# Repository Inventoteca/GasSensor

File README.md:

# Gas Sensor
Sensor de nivel de gas para tanques estacionarios. Se coloca sobre 
el indicador de nivel y transmite las lectura de manera inalámbrica. 
Hay 2 versiones principales: uno que usa LoRa y otro que usa Sigfox.  

La versión LoRa no es viable porque necesita muchas estaciones disponibles.  
La versión Sigfox funciona.  

Debe funcionar durante 3 años continuos usando 2 baterías AA. 
Se necesita un consumo promedio de 4 mA o menos.

El diseño "sensor_sigfox_1.1" es una actualización de la versión 1 del sensor Sigfox. 
Se han realizado cmabios en hardware y software . Los cambios principales son:  
- los módulos están configurados en modo de bajo consumo
- la lectura del voltaje de alimentación se realiza con el hardware interno del microcontrolador (de esta forma se elimina un divisor de voltaje externo)
- cambio de sensor magnético (se descarta el AS5600 y se agrega el MLX90393)
- usar frecuencia de reloj de ultra-bajo consumo (32.768 kHz)
- se puede usar el generador de frecuencia interno, pero también se agrega un cristal y capacitores de carga para commparar el consumo
- eliminar booster
- agregar conector U.FL para antena y pad para soldar antena de alambre opcional (eliminar conector SMA)

El conector U.FL se usa en muchos dispositivos  
https://en.wikipedia.org/wiki/Hirose_U.FL  
https://learn.sparkfun.com/tutorials/three-quick-tips-about-using-ufl/all  
https://www.data-alliance.net/ufl-cables/  

Los cristales más baratos tienen encapsulado cilindrico  
https://www.lcsc.com/product-detail/Crystals_CREC-01-X-TB-11CHJRI032768000_C7462599.html  
Para facilitar el montaje se usarán cristales SMD aunque son un poco más grandes  
https://www.lcsc.com/product-detail/Crystals_huaxindianzi-DP2032K76812001_C17702403.html  

El microcontrolador es ATtiny826 (8kB, family 2, 20 pins). Se usan los siguiente pines:  
- alimentación VCC pin 1, GND pin 20
- I2C (TWI) SDA pin 10 PB1, SCL pin 11 PB0
- cristal TOSC1 pin 8 PB3, TOSC2 pin 9 PB2
- UART hay 2 puertos con pines configurables (Serial y Serial1) con TX, RX, XCK, XDIR en PC0, PC1, PC2, PC3 y PA1, PA2, PA3, PA4
https://datasheet.lcsc.com/lcsc/2309071123_Microchip-Tech-ATTINY826-XU_C3235639.pdf
https://github.com/SpenceKonde/megaTinyCore

Los componentes más baratos están en LCSC, luego DigiKey y en tercer lugar Mouser  

El sensor Hall se puede usar en modo I2C o SPI. Se usará el modo I2C

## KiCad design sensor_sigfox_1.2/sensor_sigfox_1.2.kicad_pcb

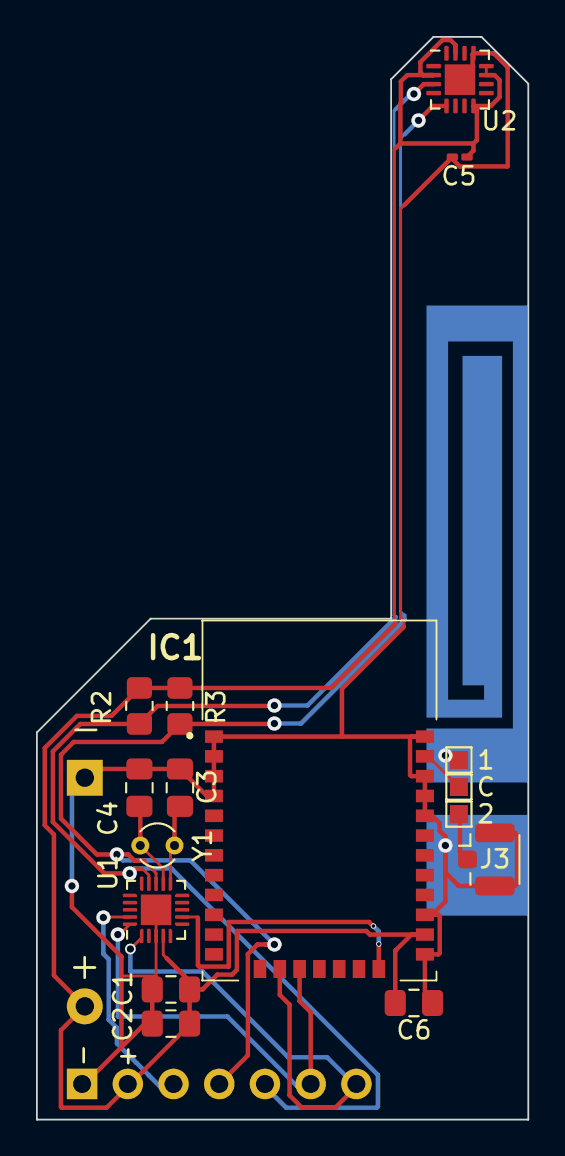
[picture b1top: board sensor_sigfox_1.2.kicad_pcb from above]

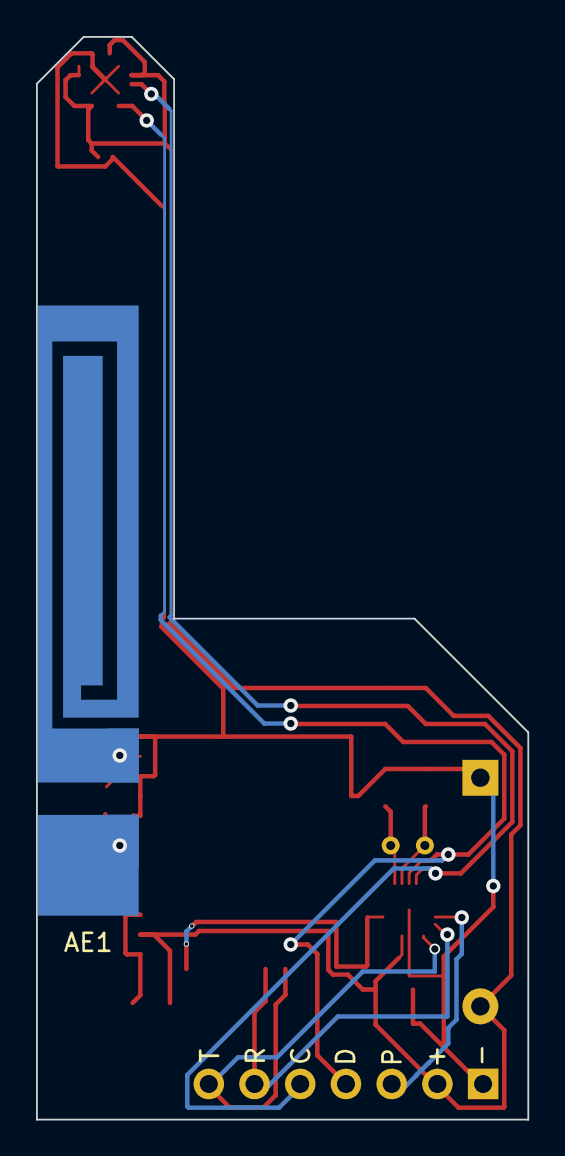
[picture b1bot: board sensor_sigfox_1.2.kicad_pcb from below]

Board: 2 copper layers, 27.3 x 60.1 mm, 19 parts (2 on the bottom side), 13 nets.

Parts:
1, 2: TestPoint; TestPoint_Pad_1.0x1.0mm
AE1: Antenna_Shield; antena1
C: TestPoint; TestPoint_Pad_1.0x1.0mm
C1: 10u; C_0805_2012Metric_Pad1.18x1.45mm_HandSolder
C2, C6: 100n; C_0805_2012Metric_Pad1.18x1.45mm_HandSolder
C3, C4: 20p; C_0805_2012Metric_Pad1.18x1.45mm_HandSolder
C5: 100n; C_0201_0603Metric_Pad0.64x0.40mm_HandSolder
IC1: WSSFM11R2DAT
J1: Battery; BatteryHolder_Keystone_2468_2xAAA
J2: Conn_01x07_Socket; PinHeader_1x07_P2.54mm_Vertical
J3: Conn_Coaxial; U.FL_Hirose_U.FL-R-SMT-1_Vertical
R2, R3: 2.2k; R_0805_2012Metric_Pad1.20x1.40mm_HandSolder
U1: ATtiny826-X; VQFN-20-1EP_3x3mm_P0.4mm_EP1.7x1.7mm
U2: MLX90393; QFN-16-1EP_3x3mm_P0.5mm_EP1.7x1.7mm
Y1: 32.768 kHz; Crystal_C26-LF_D2.1mm_L6.5mm_Vertical

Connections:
/SCL: J2.5, R2.1, U1.14 (PB0), U2.3 (SCL/SCLK)
/SDA: J2.4, R3.1, U1.13 (PB1), U2.5 (SDA/MOSI)
/SF_RX: IC1.15 (UARTRX), J2.6, U1.20 (PA1)
/SF_TX: IC1.14 (UARTTX), J2.7, U1.1 (PA2)
GND: AE1.2 (Shield), C1.1, C2.1, C3.1, C4.1, C5.1, C6.1, IC1.1 (GND_1), IC1.2 (GND_2), IC1.3 (GND_3), IC1.4 (GND_4), IC1.20 (GND_5), IC1.22 (GND_6), IC1.27 (GND_7), IC1.28 (GND_8), IC1.29 (GND_9), IC1.31 (GND_10), J1.1, J2.1, J3.2 (Ext), U1.3 (GND), U1.21 (GND), U2.13 (VSS), U2.17 (PAD)
unnamed: 1.1, AE1.1 (A)
unnamed: C.1, IC1.30 (RF_IO)
unnamed: IC1.19 (RST_N), U1.7 (PA6)
unnamed: J2.3, U1.19 (~RESET/PA0)
unnamed: 2.1, J3.1 (In)
unnamed: C4.2, U1.12 (PB2), Y1.2
unnamed: C3.2, U1.11 (PB3), Y1.1
VCC: C1.2, C2.2, C5.2, C6.2, IC1.21 (VDD_IO), J1.2, J2.2, R2.2, R3.2, U1.4 (VCC), U2.2 (MS/CS), U2.8 (VDD_IO), U2.11 (A1), U2.12 (A0), U2.15 (VDD)

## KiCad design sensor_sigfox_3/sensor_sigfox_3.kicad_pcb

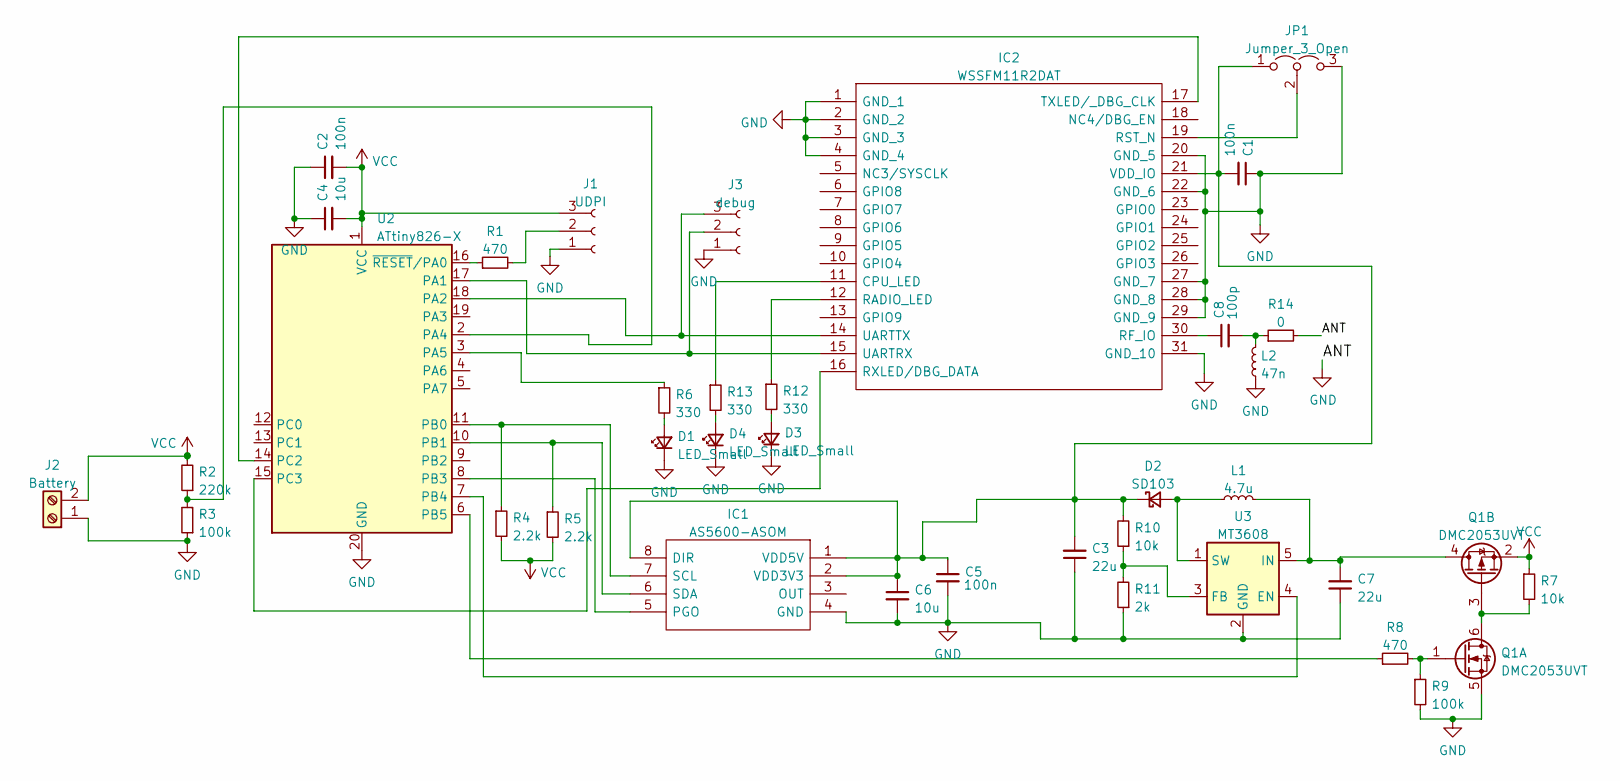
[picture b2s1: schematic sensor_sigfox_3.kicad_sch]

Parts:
C1, C2, C5: 100n; C_0603_1608Metric_Pad1.08x0.95mm_HandSolder
C3, C7: 22u; C_0805_2012Metric_Pad1.18x1.45mm_HandSolder
C4, C6: 10u; C_0603_1608Metric_Pad1.08x0.95mm_HandSolder
C8: 100p; C_0603_1608Metric_Pad1.08x0.95mm_HandSolder
D1, D3, D4: LED_Small; LED_0603_1608Metric_Pad1.05x0.95mm_HandSolder
D2: SD103; D_SMA
IC1: AS5600-ASOM; SOIC127P600X175-8N; Manufacturer_Part_Number AS5600-ASOM; Mouser Part Number 985-AS5600-ASOM
IC2: WSSFM11R2DAT; Manufacturer_Part_Number WSSFM11R2DAT
J1: UDPI; PinHeader_1x03_P2.54mm_Vertical
J2: Battery; PinHeader_1x02_P2.54mm_Horizontal
J3: debug; PinHeader_1x03_P2.54mm_Vertical
JP1: Jumper_3_Open; SolderJumper-3_P1.3mm_Open_Pad1.0x1.5mm
L1: 4.7u; L_Murata_LQH55DN_5.7x5.0mm
L2: 47n; L_0603_1608Metric_Pad1.05x0.95mm_HandSolder
Q1: DMC2053UVT; TSOT-23-6
R1, R8: 470; R_0603_1608Metric_Pad0.98x0.95mm_HandSolder
R2: 220k; R_0603_1608Metric_Pad0.98x0.95mm_HandSolder
R3, R9: 100k; R_0603_1608Metric_Pad0.98x0.95mm_HandSolder
R4, R5: 2.2k; R_0603_1608Metric_Pad0.98x0.95mm_HandSolder
R6, R12, R13: 330; R_0603_1608Metric_Pad0.98x0.95mm_HandSolder
R7, R10: 10k; R_0603_1608Metric_Pad0.98x0.95mm_HandSolder
R11: 2k; R_0603_1608Metric_Pad0.98x0.95mm_HandSolder
R14: 0; R_0603_1608Metric_Pad0.98x0.95mm_HandSolder
U2: ATtiny826-X; SSOP-20_5.3x7.2mm_P0.65mm
U3: MT3608; SOT-23-6

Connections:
GND: C1.1, C2.1, C3.1, C4.1, C5.2, C6.2, C7.1, D1.1 (K), D3.1 (K), D4.1 (K), IC1.4 (GND), IC2.1 (GND_1), IC2.2 (GND_2), IC2.3 (GND_3), IC2.4 (GND_4), IC2.20 (GND_5), IC2.22 (GND_6), IC2.27 (GND_7), IC2.28 (GND_8), IC2.29 (GND_9), IC2.31 (GND_10), J1.1, J2.1, J3.1, JP1.3 (B), L2.1, Q1.5 (S), R3.1, R9.2, R11.1, R14.2, U2.20 (GND), U3.2 (GND)
unnamed: C1.2, C3.2, C5.1, C6.1, D2.1 (K), IC1.1 (VDD5V), IC1.2 (VDD3V3), IC1.8 (DIR), IC2.21 (VDD_IO), JP1.1 (A), R10.2
unnamed: C7.2, L1.2, Q1.4 (D), U3.5 (IN)
unnamed: C8.2, L2.2, R14.1
unnamed: D1.2 (A), R6.2
unnamed: D2.2 (A), L1.1, U3.1 (SW)
unnamed: D3.2 (A), R12.2
unnamed: D4.2 (A), R13.2
unnamed: IC1.5 (PGO), U2.8 (PB3)
unnamed: IC1.6 (SDA), R5.1, U2.10 (PB1)
unnamed: IC1.7 (SCL), R4.1, U2.11 (PB0)
unnamed: IC2.11 (CPU_LED), R13.1
unnamed: IC2.12 (RADIO_LED), R12.1
unnamed: IC2.14 (UARTTX), J3.3, U2.18 (PA2)
unnamed: IC2.15 (UARTRX), J3.2, U2.17 (PA1)
unnamed: IC2.16 (RXLED/DBG_DATA), U2.15 (PC3)
unnamed: IC2.17 (TXLED/_DBG_CLK), U2.14 (PC2)
unnamed: IC2.19 (RST_N), JP1.2 (C)
unnamed: C8.1, IC2.30 (RF_IO)
unnamed: J1.2, R1.2
unnamed: Q1.1 (G), R8.2, R9.1
unnamed: Q1.3 (G), Q1.6 (D), R7.2
unnamed: R1.1, U2.16 (~RESET/PA0)
unnamed: R2.1, R3.2, U2.2 (PA4)
unnamed: R10.1, R11.2, U3.3 (FB)
unnamed: R6.1, U2.3 (PA5)
unnamed: R8.1, U2.6 (PB5)
unnamed: U2.7 (PB4), U3.4 (EN)
VCC: C2.2, C4.2, J1.3, J2.2, Q1.2 (S), R2.2, R4.2, R5.2, R7.1, U2.1 (VCC)

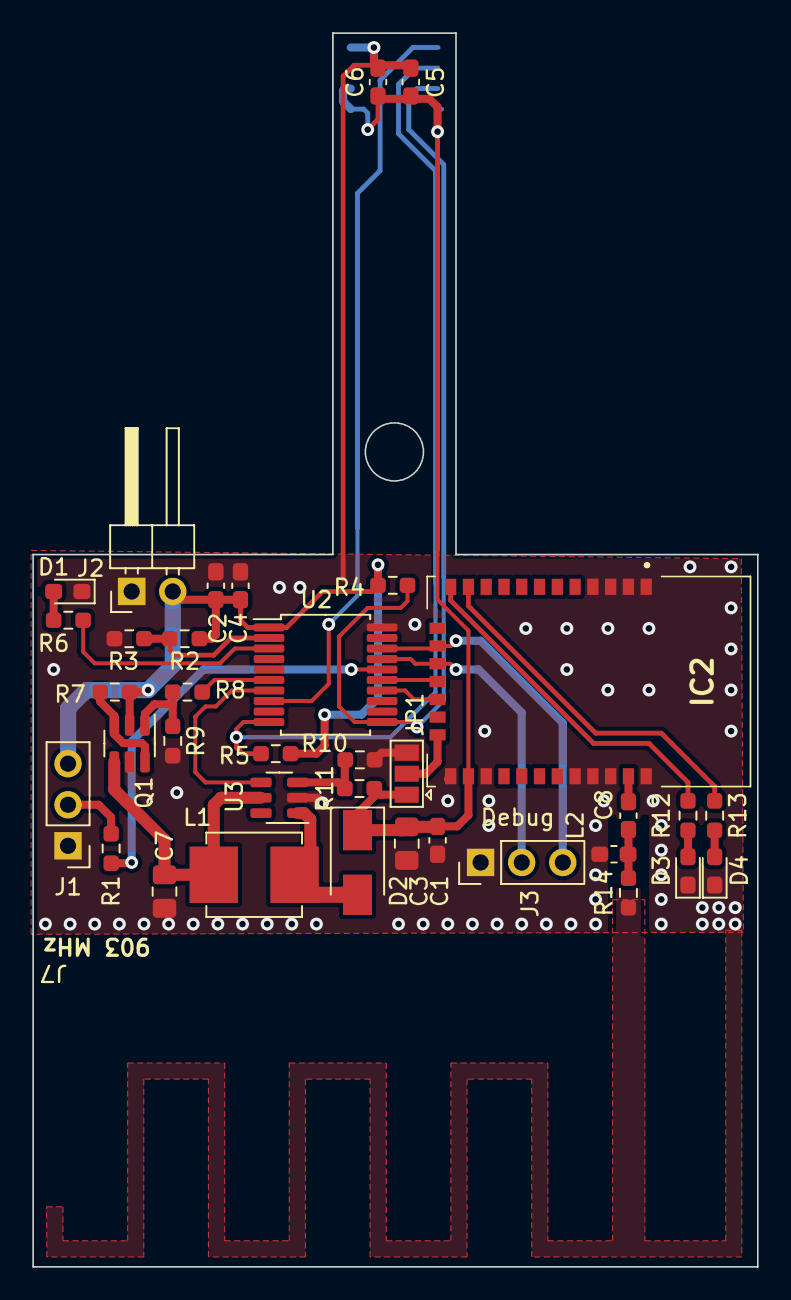
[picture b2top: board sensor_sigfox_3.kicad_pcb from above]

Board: 2 copper layers, 44.8 x 76.3 mm, 37 parts (1 on the bottom side), 29 nets.

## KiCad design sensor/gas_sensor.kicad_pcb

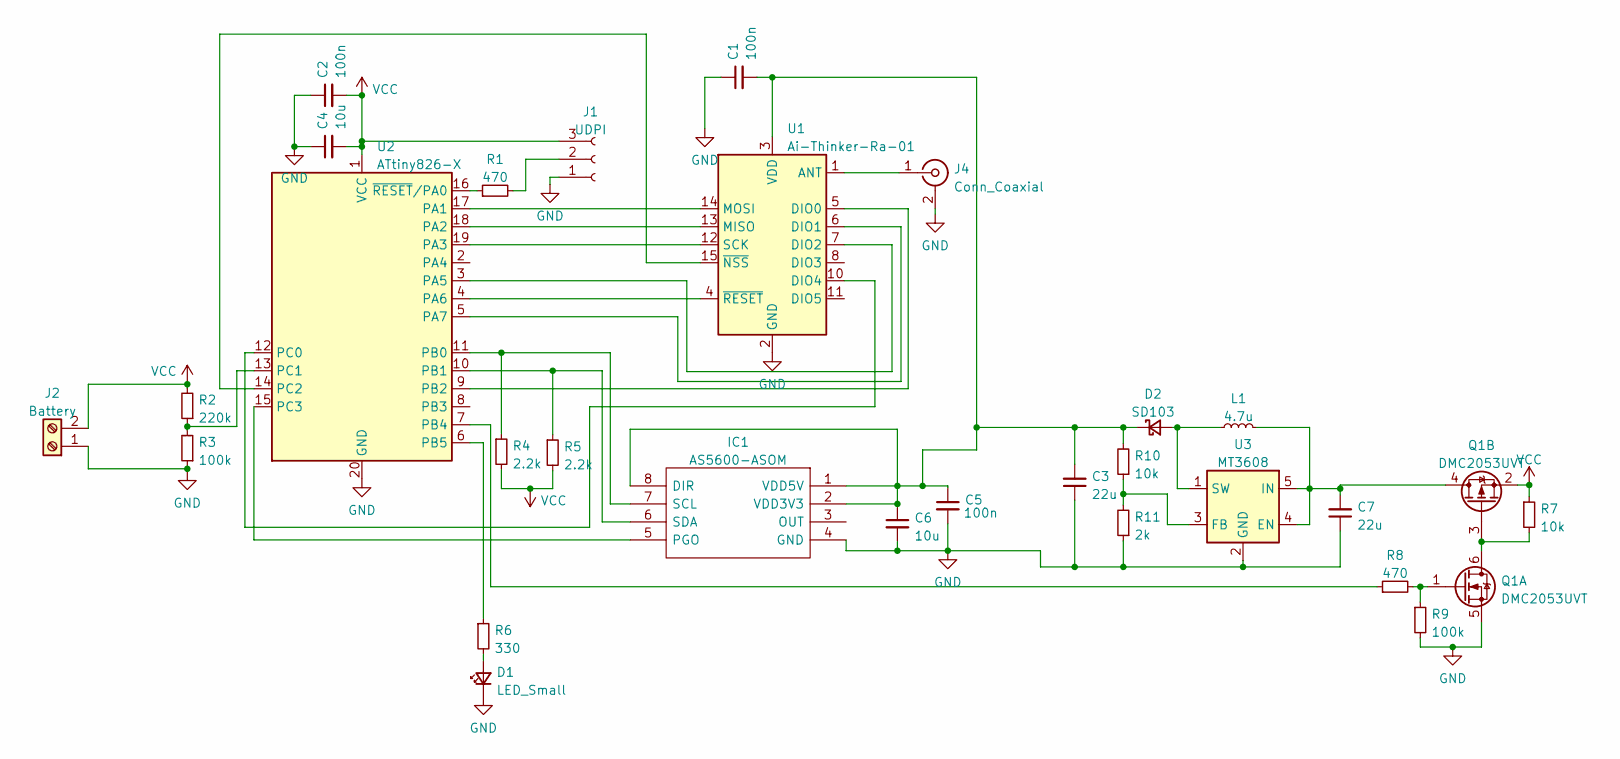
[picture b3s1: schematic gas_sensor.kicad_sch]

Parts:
C1, C2, C5: 100n; C_0805_2012Metric_Pad1.18x1.45mm_HandSolder
C3, C7: 22u; C_0805_2012Metric_Pad1.18x1.45mm_HandSolder
C4, C6: 10u; C_0805_2012Metric_Pad1.18x1.45mm_HandSolder
D1: LED_Small; LED_0603_1608Metric_Pad1.05x0.95mm_HandSolder
D2: SD103; D_SOD-323_HandSoldering
IC1: AS5600-ASOM; SOIC127P600X175-8N; Manufacturer_Part_Number AS5600-ASOM; Mouser Part Number 985-AS5600-ASOM
J1: UDPI; PinHeader_1x03_P2.54mm_Vertical
J2: Battery; PinHeader_1x02_P2.54mm_Horizontal
J4: Conn_Coaxial; SMA_Samtec_SMA-J-P-X-ST-EM1_EdgeMount
L1: 4.7u; L_0805_2012Metric_Pad1.15x1.40mm_HandSolder
Q1: DMC2053UVT; TSOT-23-6
R1, R8: 470; R_0805_2012Metric_Pad1.20x1.40mm_HandSolder
R2: 220k; R_0805_2012Metric_Pad1.20x1.40mm_HandSolder
R3, R9: 100k; R_0805_2012Metric_Pad1.20x1.40mm_HandSolder
R4, R5: 2.2k; R_0805_2012Metric_Pad1.20x1.40mm_HandSolder
R6: 330; R_0805_2012Metric_Pad1.20x1.40mm_HandSolder
R7, R10: 10k; R_0805_2012Metric_Pad1.20x1.40mm_HandSolder
R11: 2k; R_0805_2012Metric_Pad1.20x1.40mm_HandSolder
U1: Ai-Thinker-Ra-01; Ai-Thinker-Ra-01-LoRa
U2: ATtiny826-X; SSOP-20_5.3x7.2mm_P0.65mm
U3: MT3608; SOT-23-6

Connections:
GND: C1.1, C2.1, C3.1, C4.1, C5.2, C6.2, C7.1, D1.1 (K), IC1.4 (GND), J1.1, J2.1, J4.2 (Ext), Q1.5 (S), R3.1, R9.2, R11.1, U1.2 (GND), U1.9 (GND), U1.16 (GND), U2.20 (GND), U3.2 (GND)
unnamed: C1.2, C3.2, C5.1, C6.1, D2.1 (K), IC1.1 (VDD5V), IC1.2 (VDD3V3), IC1.8 (DIR), R10.2, U1.3 (VDD)
unnamed: D1.2 (A), R6.2
unnamed: D2.2 (A), L1.1, U3.1 (SW)
unnamed: IC1.5 (PGO), U2.15 (PC3)
unnamed: IC1.6 (SDA), R5.1, U2.10 (PB1)
unnamed: IC1.7 (SCL), R4.1, U2.11 (PB0)
unnamed: J1.2, R1.2
unnamed: J4.1 (In), U1.1 (ANT)
unnamed: Q1.1 (G), R8.2, R9.1
unnamed: Q1.3 (G), Q1.6 (D), R7.2
unnamed: C7.2, L1.2, Q1.4 (D), U3.4 (EN), U3.5 (IN)
unnamed: R1.1, U2.16 (~RESET/PA0)
unnamed: R2.1, R3.2, U2.13 (PC1)
unnamed: R6.1, U2.6 (PB5)
unnamed: R8.1, U2.7 (PB4)
unnamed: R10.1, R11.2, U3.3 (FB)
unnamed: U1.4 (~RESET), U2.4 (PA6)
unnamed: U1.5 (DIO0), U2.9 (PB2)
unnamed: U1.6 (DIO1), U2.5 (PA7)
unnamed: U1.7 (DIO2), U2.3 (PA5)
unnamed: U1.10 (DIO4), U2.12 (PC0)
unnamed: U1.12 (SCK), U2.19 (PA3)
unnamed: U1.13 (MISO), U2.18 (PA2)
unnamed: U1.14 (MOSI), U2.17 (PA1)
unnamed: U1.15 (~NSS), U2.14 (PC2)
VCC: C2.2, C4.2, J1.3, J2.2, Q1.2 (S), R2.2, R4.2, R5.2, R7.1, U2.1 (VCC)

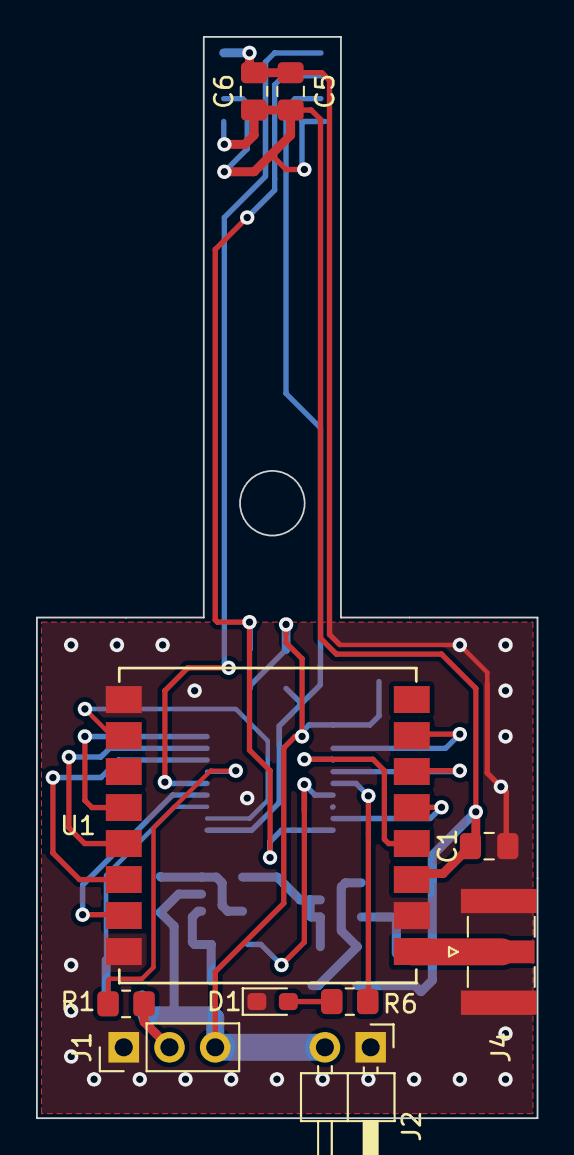
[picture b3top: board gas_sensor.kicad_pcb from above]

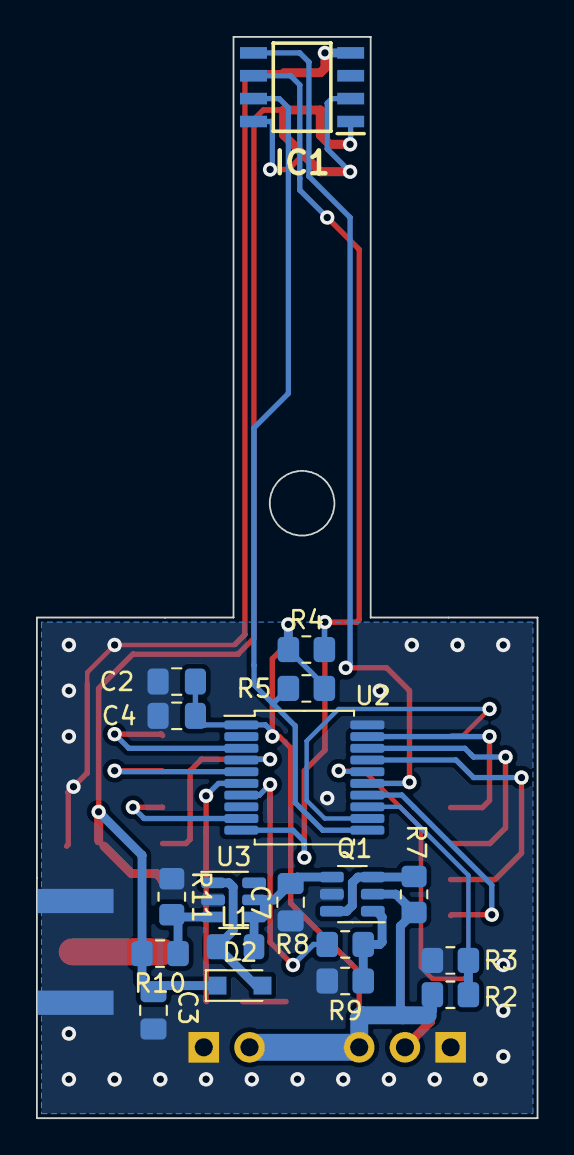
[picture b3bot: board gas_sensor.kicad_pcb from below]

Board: 2 copper layers, 27.8 x 60.1 mm, 29 parts (19 on the bottom side), 27 nets.

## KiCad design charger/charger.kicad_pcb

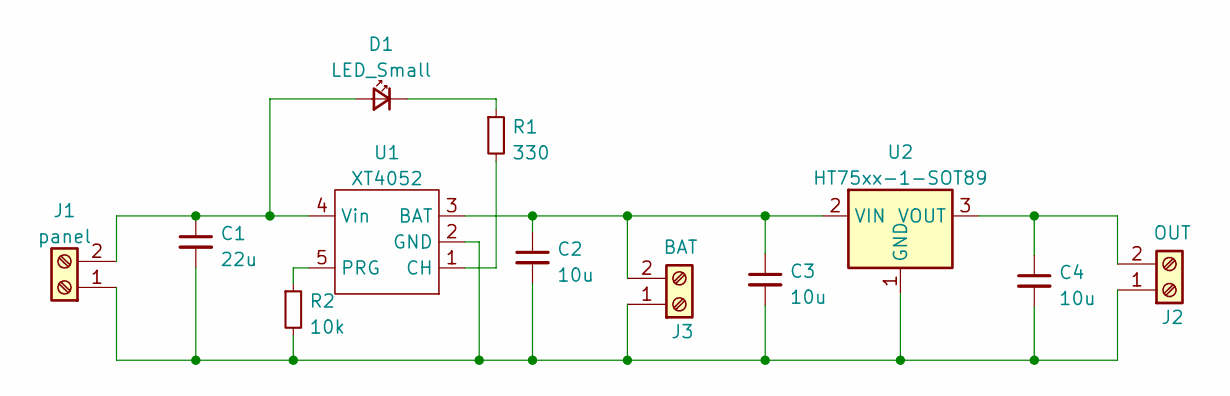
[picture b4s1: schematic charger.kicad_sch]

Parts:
C1: 22u; C_0805_2012Metric_Pad1.18x1.45mm_HandSolder
C2, C3, C4: 10u; C_0805_2012Metric_Pad1.18x1.45mm_HandSolder
D1: LED_Small; LED_0603_1608Metric_Pad1.05x0.95mm_HandSolder
J1: panel; TerminalBlock_bornier-2_P5.08mm
J2: OUT; TerminalBlock_bornier-2_P5.08mm
J3: BAT; TerminalBlock_bornier-2_P5.08mm
R1: 330; R_0805_2012Metric_Pad1.20x1.40mm_HandSolder
R2: 10k; R_0805_2012Metric_Pad1.20x1.40mm_HandSolder
U1: XT4052; SOT-23-5_HandSoldering
U2: HT75xx-1-SOT89; SOT-89-3

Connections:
unnamed: C1.1, D1.2 (A), J1.2, U1.4 (Vin)
unnamed: C1.2, C2.2, C3.2, C4.2, J1.1, J2.1, J3.1, R2.2, U1.2 (GND), U2.1 (GND)
unnamed: C2.1, C3.1, J3.2, U1.3 (BAT), U2.2 (VIN)
unnamed: C4.1, J2.2, U2.3 (VOUT)
unnamed: D1.1 (K), R1.1
unnamed: R1.2, U1.1 (CH)
unnamed: R2.1, U1.5 (PRG)

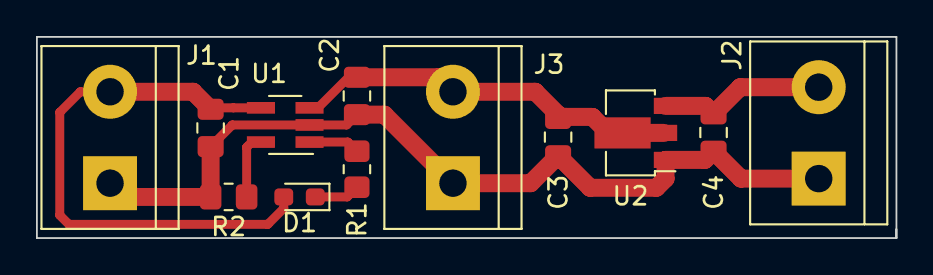
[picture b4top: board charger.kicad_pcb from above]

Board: 2 copper layers, 47.8 x 11.2 mm, 12 parts (0 on the bottom side), 7 nets.

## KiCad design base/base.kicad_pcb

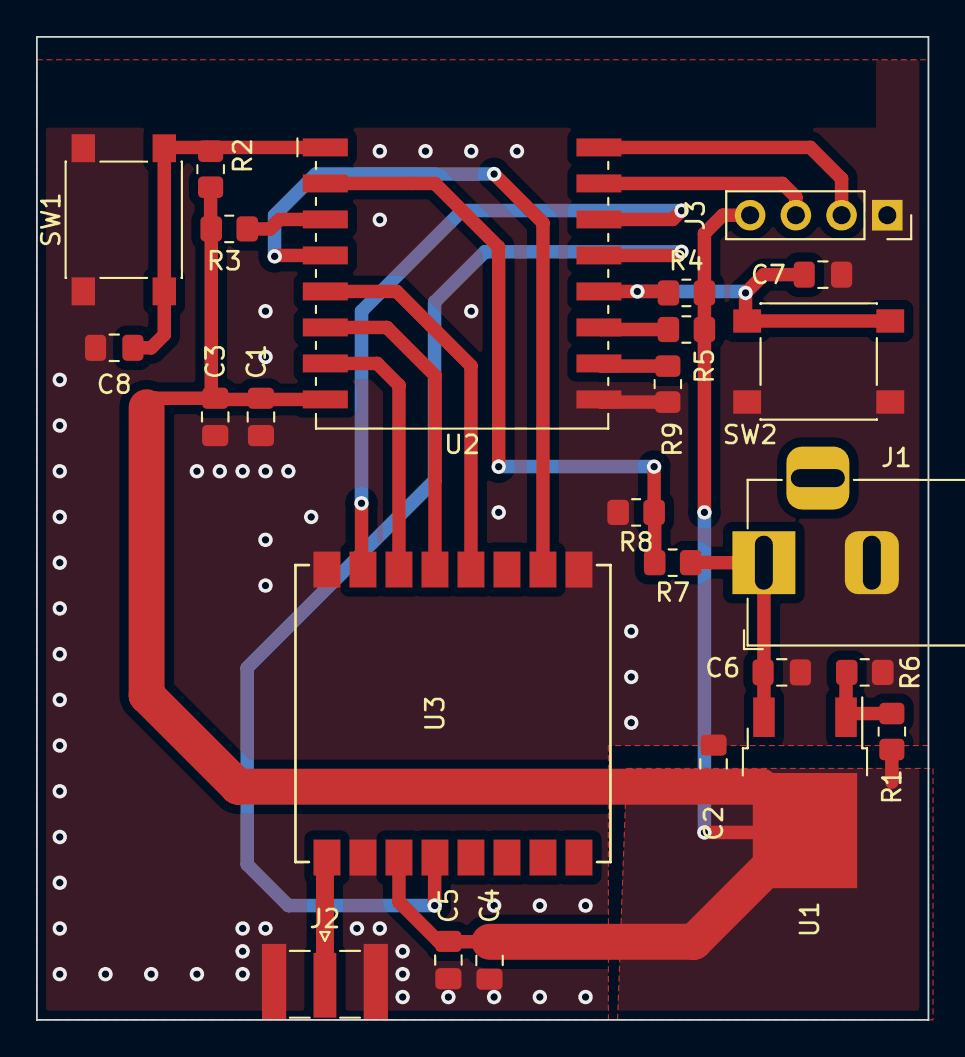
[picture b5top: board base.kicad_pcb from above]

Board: 2 copper layers, 49.5 x 54.6 mm, 25 parts (0 on the bottom side), 19 nets.

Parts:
C1, C4, C6: 10u; C_0805_2012Metric_Pad1.18x1.45mm_HandSolder
C2: 22u; C_0805_2012Metric_Pad1.18x1.45mm_HandSolder
C3, C5, C7, C8: 0.1u; C_0805_2012Metric_Pad1.18x1.45mm_HandSolder
J1: Supply; BarrelJack_Horizontal
J2: RF; SMA_Samtec_SMA-J-P-X-ST-EM1_EdgeMount
J3: PROG; PinSocket_1x04_P2.54mm_Vertical
R1, R6: 150; R_0805_2012Metric_Pad1.20x1.40mm_HandSolder
R2, R3, R4, R5, R7, R9: 10k; R_0805_2012Metric_Pad1.20x1.40mm_HandSolder
R8: 3.9k; R_0805_2012Metric_Pad1.20x1.40mm_HandSolder
SW1: Reset; SW_Push_1P1T_NO_6x6mm_H9.5mm
SW2: Flash; SW_Push_1P1T_NO_6x6mm_H9.5mm
U1: AZ1117D-ADJ; TO-252-2
U2: ESP-07
U3: Ai-Thinker-Ra-01; Ai-Thinker-Ra-01-LoRa

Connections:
/BUSY: U2.4 (GPIO16), U3.10 (DIO4)
GND: C1.1, C2.1, C3.1, C4.1, C5.1, C6.1, C7.2, C8.1, J1.2, J2.2 (Ext), J3.1, R6.2, R8.2, R9.2, SW1.1, SW2.2, U2.9 (GND), U3.2 (GND), U3.9 (GND), U3.16 (GND)
unnamed: C1.2, C2.2, C3.2, C4.2, C5.2, J3.4, R1.1, R2.1, R3.1, R4.1, R5.1, U1.2 (VO), U2.8 (VCC), U3.3 (VDD)
unnamed: C6.2, J1.1, R7.1, U1.3 (VI)
unnamed: C7.1, R4.2, SW2.1, U2.12 (GPIO0)
unnamed: C8.2, R2.2, SW1.2, U2.1 (~RST)
unnamed: J2.1 (In), U3.1 (ANT)
unnamed: J3.2, U2.16 (GPIO1/TXD)
unnamed: J3.3, U2.15 (GPIO3/RXD)
unnamed: R1.2, R6.1, U1.1 (ADJ)
unnamed: R3.2, U2.3 (EN)
unnamed: R5.2, U2.11 (GPIO2)
unnamed: R7.2, R8.1, U2.2 (ADC)
unnamed: R9.1, U2.10 (GPIO15)
unnamed: U2.5 (GPIO14), U3.12 (SCK)
unnamed: U2.6 (GPIO12), U3.13 (MISO)
unnamed: U2.7 (GPIO13), U3.14 (MOSI)
unnamed: U2.13 (GPIO4), U3.4 (~RESET)
unnamed: U2.14 (GPIO5), U3.15 (~NSS)

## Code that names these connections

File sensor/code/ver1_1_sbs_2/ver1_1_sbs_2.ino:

#include <SPI.h>
#include <Ra01S.h>
#include <AS5600.h>
#include <EEPROM.h>
#include <avr/sleep.h>
//#define RF_FREQUENCY                                433000000 // Hz  center frequency
//#define RF_FREQUENCY                                866000000 // Hz  center frequency
#define RF_FREQUENCY                                915000000 // Hz  center frequency
#define TX_OUTPUT_POWER                             22        // dBm tx output power
#define LORA_BANDWIDTH                              4         // bandwidth
                                                              // 2: 31.25Khz
                                                              // 3: 62.5Khz
                                                              // 4: 125Khz
                                                              // 5: 250KHZ
                                                              // 6: 500Khz                                                               
#define LORA_SPREADING_FACTOR                       7         // spreading factor [SF5..SF12]
#define LORA_CODINGRATE                             1         // [1: 4/5,
                                                              //  2: 4/6,
                                                              //  3: 4/7,
                                                              //  4: 4/8]

#define LORA_PREAMBLE_LENGTH                        8         // Same for Tx and Rx
#define LORA_PAYLOADLENGTH                          0         // 0: Variable length packet (explicit header)
                                                              // 1..255  Fixed length packet (implicit header)
//#define PERIOD      10 
#define PERIOD      900 //15 min
#define ALA         200
#define LED         PIN_PB5
#define PWR         PIN_PB4
#define BAT         PIN_PC1

#define DIO1        PIN_PA7
#define DIO2        PIN_PA5

//#define SDIR        PIN_PB3
#define SPGO        PIN_PC3
#define SOUT        PIN_PC0

//#if 1
/*
 * for ATmega328/2560
 * VCC    3V3/3V3
 * GND    GND/GND
 * SCK    13/52
 * MISO   12/50
 * MOSI   11/51
 * NSS     5/5
 * RST     6/6
 * BUSY    7/7
 */
uint16_t ang_old=0, ang=0, bat=0;
uint8_t txData[9], rxData[4];
uint8_t rxLen=0, hops=0;
volatile uint16_t count=0;
boolean stat=0, note=0;
AS5600 encoder;
SX126x  lora(PIN_PC2,               //Port-Pin Output: SPI select
             PIN_PA6,               //Port-Pin Output: Reset 
             PIN_PB3                //Port-Pin Input:  Busy
             );

//#endif // ATmega328/2560

void RTC_init(void)
{
  /* Initialize RTC: */
  while (RTC.STATUS > 0)
  {
    ;                                   /* Wait for all register to be synchronized */
  }
  RTC.CLKSEL = RTC_CLKSEL_INT32K_gc;    /* 32.768kHz Internal Ultra-Low-Power Oscillator (OSCULP32K) */

  RTC.PITINTCTRL = RTC_PI_bm;           /* PIT Interrupt: enabled */

  RTC.PITCTRLA = RTC_PERIOD_CYC32768_gc /* RTC Clock Cycles 16384, resulting in 32.768kHz/16384 = 2Hz */
  | RTC_PITEN_bm;                       /* Enable PIT counter: enabled */
}

ISR(RTC_PIT_vect)
{
  RTC.PITINTFLAGS = RTC_PI_bm;          /* Clear interrupt flag by writing '1' (required) */
  count++;
}


void setup() 
{
  RTC_init(); 
  EEPROM.write(0, 'a');
  EEPROM.write(1, 'b');
  EEPROM.write(2, 'c');
  EEPROM.write(3, 4);
  pinMode(LED, OUTPUT);
  pinMode(PWR, OUTPUT);
  //pinMode(SDIR, OUTPUT);
  pinMode(SPGO, OUTPUT);
  pinMode(BAT, INPUT);
  pinMode(DIO1, INPUT);
  pinMode(DIO2, INPUT);
  pinMode(SOUT, INPUT);
  analogReference(INTERNAL2V048);
  txData[0] = EEPROM.read(0);        
  txData[1] = EEPROM.read(1);
  txData[2] = EEPROM.read(2);
  txData[3] = EEPROM.read(3);// ID, 4bytes
  digitalWrite(PWR, 1);//always on
  //digitalWrite(SDIR, 1);
  digitalWrite(SPGO, 1);
  SPI.begin();
  digitalWrite(LED, 1);
  delay(500);
  digitalWrite(LED, 0);
  delay(500);
  digitalWrite(LED, 1);
  delay(500);
  digitalWrite(LED, 0);
  delay(500);

  //lora.DebugPrint(true);

  int16_t ret = lora.begin(RF_FREQUENCY,              //frequency in Hz
                           TX_OUTPUT_POWER);          //tx power in dBm
  if (ret != ERR_NONE) while(1) {
    delay(1);
    digitalWrite(LED, 1);
    delay(100);
    digitalWrite(LED, 0);
    delay(100);
    }


  lora.LoRaConfig(LORA_SPREADING_FACTOR, 
                  LORA_BANDWIDTH, 
                  LORA_CODINGRATE, 
                  LORA_PREAMBLE_LENGTH, 
                  LORA_PAYLOADLENGTH, 
                  true,               //crcOn  
                  false);             //invertIrq
reg:
  if (lora.Send(txData, 4, SX126x_TXMODE_SYNC)) {
    //digitalWrite(LED, 1);
    //delay(1000);
    //digitalWrite(LED, 0);
     while(rxLen<=0){
      rxLen = lora.Receive(rxData, 4);
     }
    if((rxData[0]==txData[0])&&(rxData[1]==txData[1])&&(rxData[2]==txData[2])&&(rxData[3]==txData[3])){
      digitalWrite(LED, 1);
      delay(1000);
      digitalWrite(LED, 0);
     }
     else goto reg;
     
  } else {
    while(1){
      digitalWrite(LED, 1);
      delay(300);
      digitalWrite(LED, 0);
      delay(300);
    }
  }
  /*
  while(rxLen<=0){
    rxLen = lora.Receive(rxData, 4);
  }
  if((rxData[0]==txData[0])&&(rxData[1]==txData[1])&&(rxData[2]==txData[2])&&(rxData[3]==txData[3])){
    digitalWrite(LED, 1);
    delay(1000);
    digitalWrite(LED, 0);
  }
  else goto reg;*/
  ang_old = encoder.getAngle();
  set_sleep_mode(SLEEP_MODE_PWR_DOWN);  /* Set sleep mode to POWER DOWN mode */
  digitalWrite(PWR, 0);
  delay(5000);
}


void loop() 
{
 slp:
  sleep_cpu();
  if (count<PERIOD) goto slp;
  uint8_t txData[10];
  //sprintf((char *)txData, "Hello World %lu", millis());
  //ADC0.CTRLA |= ~ADC_ENABLE_bm;
  digitalWrite(PWR, 1);
  txData[0] = EEPROM.read(0);        
  txData[1] = EEPROM.read(1);
  txData[2] = EEPROM.read(2);
  txData[3] = EEPROM.read(3);// ID, 4bytes
  ang = encoder.getAngle();
  if (ang >4000){
    //ADC0.CTRLA &= ~ADC_ENABLE_bm;
    digitalWrite(PWR, 0);
    goto slp;
  }
  bat=analogRead(BAT);
  txData[5] = ang & 0xFF;         // extract least significant byte
  txData[4] = (ang >> 8) & 0xFF;  // extract most significant byte
  txData[7] = bat & 0xFF;         // extract least significant byte
  txData[6] = (bat >> 8) & 0xFF;  // extract most significant byte
  //uint8_t len = strlen((char *)txData);
  if (ang_old < ang){
    if ((ang - ang_old)>ALA){
      txData[8]=2;
      note=1;
    }
    else {
      txData[8]=0;
      note=0;
    }
  }
  else if (ang_old > ang){
    if ((ang_old - ang)>ALA){
      txData[8]=1;
      note=1;
    }
    else {
      txData[8]=0;
      note=0;
    }
  }
  else {
    txData[8]=0;
    note=0;
  }
  ang_old = ang;
  // Wait for transmission to complete
sending:  
  if (note==1){
    stat=lora.Send(txData, 9, SX126x_TXMODE_SYNC);
  }
  else{
    stat=lora.Send(txData, 8, SX126x_TXMODE_SYNC);
  }
  if(stat==0){//problem
    digitalWrite(LED, 1);
    delay(5000);
    digitalWrite(LED, 0);
    //delay(300);
    //digitalWrite(LED, 1);
    //delay(300);
    //digitalWrite(LED, 0);
  }
  else{
    hops++;
    unsigned long start_time=millis();
    while((rxLen<=0)&&((millis()-start_time)<3000)){
      rxLen = lora.Receive(rxData, 4); 
      if((rxData[0]==txData[0])&&(rxData[1]==txData[1])&&(rxData[2]==txData[2])&&(rxData[3]==txData[3])){
        break;
      }
      else rxLen=-1;
    }
    if(((millis()-start_time)>3000)&&(hops<3)){
      goto sending;
    }
    else(hops=0);
  }
  digitalWrite(PWR, 0);
  //ADC0.CTRLA &= ~ADC_ENABLE_bm;
  digitalWrite(LED, 1);
  delay(100);
  digitalWrite(LED, 0);
  count=0;
  
  // Do not wait for the transmission to be completed
  //lora.Send(txData, len, SX126x_TXMODE_ASYNC );

  //delay(2000);
}

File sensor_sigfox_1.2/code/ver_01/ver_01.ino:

#include <AS5600.h>
#include <avr/sleep.h>
#include <EEPROM.h>

#define idTag             1234 // set id
#define sleepTimerTime    10 // time sleep in second
                              // 1 hour 3600 second 

#define bataryPIN         PIN_PA4     //
#define SPGO              PIN_PB3
#define PWR               PIN_PB4
#define LED_D1            PIN_PA3


uint16_t angel, bataryVoltage;
uint8_t dataToSend[10];

volatile uint16_t countRTC_CLK=0;

bool verifiedSendData = false;
AS5600 encoder; 



void RTC_init(void)
{
  /* Initialize RTC: */
  while (RTC.STATUS > 0)
  {
    ;                                   /* Wait for all register to be synchronized */
  }
  RTC.CLKSEL = RTC_CLKSEL_INT32K_gc;    /* 32.768kHz Internal Ultra-Low-Power Oscillator (OSCULP32K) */

  RTC.PITINTCTRL = RTC_PI_bm;           /* PIT Interrupt: enabled */

  RTC.PITCTRLA = RTC_PERIOD_CYC32768_gc /* RTC Clock Cycles 32768, resulting in 32.768kHz/32768 = 1Hz */
  | RTC_PITEN_bm;                       /* Enable PIT counter: enabled */
}

ISR(RTC_PIT_vect)
{
  RTC.PITINTFLAGS = RTC_PI_bm;          /* Clear interrupt flag by writing '1' (required) */
  countRTC_CLK++;
}





void setup() {
  // put your setup code here, to run once:

  RTC_init();
  EEPROM.write(0, 'a');
  EEPROM.write(1, 'b');
  EEPROM.write(2, 'c');
  EEPROM.write(3, 1);
  analogReference(INTERNAL2V048);
  Serial1.begin(9600); // START UART
  pinMode(bataryPIN, INPUT);

  pinMode(PWR, OUTPUT);
  digitalWrite(PWR, 1);//always off , on only wakeup
  
  pinMode(SPGO, OUTPUT);
  digitalWrite(SPGO, 1);

  pinMode(LED_D1, OUTPUT);
  digitalWrite(LED_D1, 1);
  delay(500);
  digitalWrite(LED_D1, 0);    
  delay(500);
  digitalWrite(LED_D1, 1);
  delay(500);
  digitalWrite(LED_D1, 0);    
  delay(500);
  dataToSend[0] = EEPROM.read(0);        
  dataToSend[1] = EEPROM.read(1);
  dataToSend[2] = EEPROM.read(2);
  dataToSend[3] = EEPROM.read(3);
  set_sleep_mode(SLEEP_MODE_PWR_DOWN);  
    Serial1.print("AT\r");
    delay(500);
    Serial1.print("AT$I=10\r");
    delay(1000);
    Serial1.print("AT$I=11\r");
    delay(1000);
    Serial1.print ("AT$SF=023203ff\r");
    delay(10000);
    
    Serial1.print("AT$CW=923200000, 1 , 14");
    delay(100000);
    //while(1){
      //}
  //delay (3000);
}

void loop() {
      // put your main code here, to run repeatedly:
      //loop for test begin
      //use   digitalWrite(LED_D1, 1/0) if necessary 
      //or use Serial1.println (""); 
    /*  
    digitalWrite(PWR, 1);
    delay(3000);  
    Serial1.print ("AT$SF=testmesage\r");
    delay(300);
    CheckSendData();
    for (int i=0; i<3;i++){if (verifiedSendData == 0){Serial1.print ("AT$SF=testmesage\r");delay(3000);CheckSendData();delay(3000);}}
    digitalWrite(PWR, 0);
    SleepInDownModeInterruptRTC();
    */
    
    //loop for test end
    
    //loop for TZ begin 
    /*   
      digitalWrite(PWR, 1);
      digitalWrite(LED_D1, 1);
      delay(3000); 
      GetCurrencyData();
      SendData_write();
      CheckSendDataClean();
      if (verifiedSendData == 0){
        delay(1000);
        SendData_write();
      }
      
      //for (int i=0; i<2;i++){if (verifiedSendData == 0){SendData_write();delay(3000);CheckSendDataClean();delay(3000);}}
      //digitalWrite(PWR, 0);
      digitalWrite(LED_D1, 0);
      delay(10);
      SleepInDownModeInterruptRTC();
     */  
       //loop for TZ end
       /*
        * maybe use CheckSendDataClean() it will be better for TZ 
        */
    Serial1.print("AT$CB=100,1");
    delay(1000);
    Serial1.print("AT$CB=100,0");
    delay(1000);
      
}

void SleepInDownModeInterruptRTC(){
  
  while (countRTC_CLK<sleepTimerTime){sleep_cpu();}
  countRTC_CLK=0;
  
  }


void GetCurrencyData(){

  angel= encoder.getAngle();
  //delay(100);
  bataryVoltage= analogRead(bataryPIN);
  }

void SendData_write(){
  
  dataToSend[4] = (angel >> 8) & 0xFF; 
  dataToSend[5] = angel & 0xFF; 

  dataToSend[6] = (bataryVoltage >> 8) & 0xFF; 
  dataToSend[7] = bataryVoltage & 0xFF; 

  //dataToSend[4] = (idTag >> 8) & 0xFF; 
  //dataToSend[5] = idTag & 0xFF; 

  Serial1.print ("AT$SF=");
  for(byte j=0;j<8;j++){
    Serial1.write (dataToSend[j]);
  }
  //Serial1.print ("AT$SF=\r");  `  //????
  Serial1.print ("\r");          //????^^^^
  }

void CheckSendData(){
    delay (100);
    if (Serial1.available()>0){
      verifiedSendData = false;
      char in_Serial1_data  = Serial1.read();
      //Serial1.println(in_Serial1_data);
      
      if (in_Serial1_data == 'O'){
        //Serial1.println("verifed");
        verifiedSendData = true;
        //Serial1.println(verifiedSendData);
        }  
      else{
        verifiedSendData = false;
        //Serial1.println("notVerifed");
        //Serial1.println(verifiedSendData);
      }
        
    delay (1);
    
    while(Serial1.available()>0){
      Serial1.read();
      //Serial1.println("cleaning");
      delay (1);
    }
    }
}

  
void CheckSendDataClean(){
    delay (100);
    if (Serial1.available()>0){
      verifiedSendData = false;
      char in_Serial1_data  = Serial1.read();
      if (in_Serial1_data == 'O'){  verifiedSendData = true;  }
        
    delay (5);
    
    while(Serial1.available()>0){
      Serial1.read();
      delay (5);
                               }
    }}


    

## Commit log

2023-12-05 subir diseño de la "base" LoRa
2023-12-05 subir diseño de cargador LoRa
2023-12-05 subir diseño de sensor LoRa
2023-12-05 subir diseño de sensor sigfox v1
2023-12-05 subir diseño de sensor sigfox v2
2023-12-05 subir diseño de sensor sigfox v3
2023-12-05 copiar diseño sigfox_1 y agregar otro sensor y cristal
2023-12-06 iniciar conexiones a nuevos comps
2023-12-06 notas sobre pines utilizados
2023-12-08 componentes borrados
2023-12-12 wip pcb new
2023-12-13 wip almost ready
2023-12-16 low almost 5.3mA, not rtc internal change
2023-12-18 pcb wip
2023-12-18 sigfox
2023-12-18 v1.1
2024-01-24 revision 1.1.1
2024-05-27 pcb 1.1
2024-05-28 WIP on main
2024-05-30 gerber y conexiones int/trig
2024-06-14 1.1 act
2024-06-14 1.2 act
2024-06-14 1.1 y 1.2 actualizados
